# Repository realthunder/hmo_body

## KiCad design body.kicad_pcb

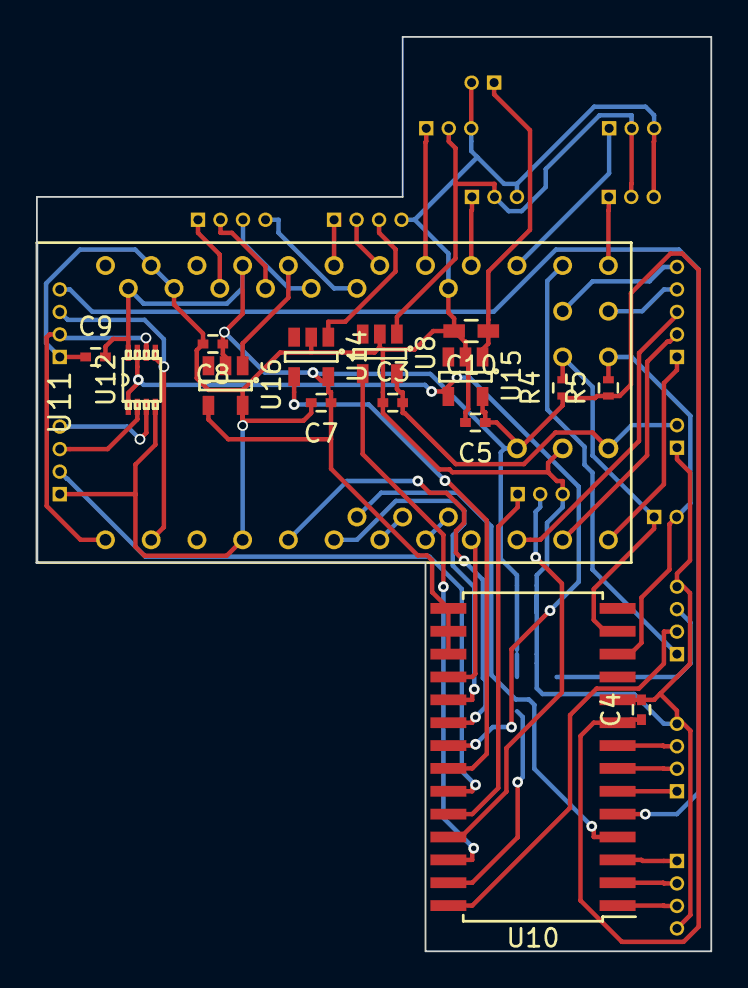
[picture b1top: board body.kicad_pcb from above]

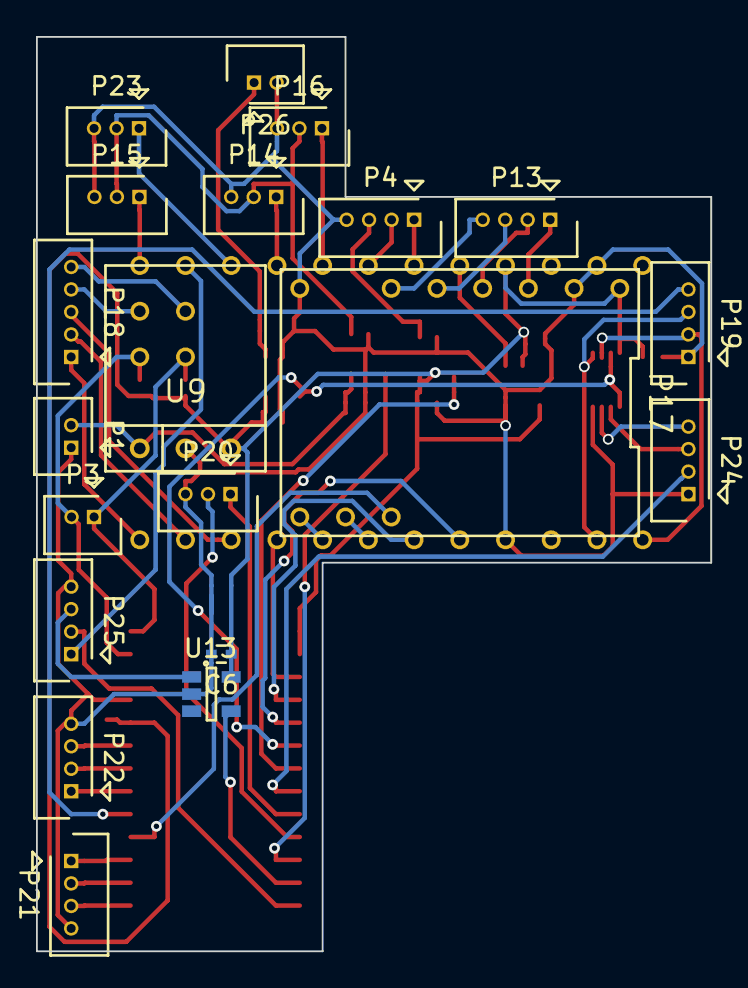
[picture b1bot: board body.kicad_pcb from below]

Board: 2 copper layers, 37.5 x 50.8 mm, 36 parts (20 on the bottom side), 51 nets.

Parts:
C3, C5, C6, C7: 1uF; C_0402
C4, C8, C9: 0.1uF; C_0402
C10: 10uF; C_0603_HandSoldering
P1: CON_VIN; Molex_PicoBlade_53047-0210
P3: CON_I2C; Molex_PicoBlade_53047-0210
P4: CON_LED; Molex_PicoBlade_53047-0410
P13: CON_STEP; Molex_PicoBlade_53047-0410
P14: CON_SRV_CAM; Molex_PicoBlade_53047-0310
P15: CON_SRV_BRAKE; Molex_PicoBlade_53047-0310
P16: CON_SRV_LOCK; Molex_PicoBlade_53047-0310
P17: CON_POLOLU_DRV8834; POLOLU_DRV8834
P18: CON_BAT; Molex_PicoBlade_53047-0510
P19: CON_UART; Molex_PicoBlade_53047-0410
P20: CON_STEP_STOP; Molex_PicoBlade_53047-0310
P21: CON_BTN2; Molex_PicoBlade_53047-0410
P22: CON_BTN1; Molex_PicoBlade_53047-0410
P23: CON_SRV_FOOT; Molex_PicoBlade_53047-0310
P24: CON_EYEPIECE_COM; Molex_PicoBlade_53047-0410
P25: CON_FAN; Molex_PicoBlade_53047-0410
P26: CON_EP_VOUT; Molex_PicoBlade_53047-0210
R4, R5: 10K; R_0402
U8: SRV_SWITCH; SOT-23-5
U9: CON_POLOLU_PWR; POLOLU_U1V10F5
U10: MCP23017; SOIC-28W_7.5x17.9mm_Pitch1.27mm
U11: ProMini; PRO_MINI
U12: 74LVC2G126; TI_DCU_8
U13: FAN_SWITCH; SOT-23-5
U14: LED_SWITCH; SOT-23-5
U15: EP_SWITCH; SOT-23-5
U16: TMP36; SOT-23-5

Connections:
/BAT1_STAT: P18.2, U11.11
/BAT1_VOUT: P18.4, U11.31
/BAT2_STAT: P18.3, U11.10
/BAT2_VOUT: P18.5, U11.32
/BAT_CTL: P18.1, U11.12
/BTN11: P22.1, U10.6
/BTN12: P22.2, U10.7
/BTN13: P22.3, U10.8
/BTN21: P21.1, U10.3
/BTN22: P21.2, U10.2
/BTN23: P21.3, U10.1
/EP_EN: U10.21, U12.1, U12.7, U15.4
/EP_RXD: P24.4, U12.3
/EP_TXD: P24.3, U12.2
/EP_VOUT: C10.1, P26.1, U15.1
/FAN_EN: U10.27, U13.4
/FAN_PWM: P25.1, U11.14
/FAN_TACHO: P25.2, U10.28
/FAN_VOUT: P25.3, U13.1
/FRAME_STOP: P24.2, U10.23
/HOST_INT: P19.4, U10.5
/INTA: U10.20, U11.5
/INTB: U10.19, U11.6
/LED_CLK: P4.1, U11.19
/LED_DAT: P4.2, U11.18
/LED_EN: U10.22, U14.4
/LED_VOUT: P4.3, U14.1
/RXD: P19.3, U11.2, U12.5
/SCL: P3.2, R5.2, U10.12, U11.40
/SDA: P3.1, R4.2, U10.13, U11.39
/SRV_BRAKE: P15.1, U11.13
/SRV_CAM: P14.1, U11.16
/SRV_EN: U8.4, U10.26
/SRV_FOOT: P23.1, U11.15
/SRV_LOCK: P16.1, U11.17
/SRV_VOUT: P14.2, P15.2, P16.2, P23.2, U8.1
/STEP: P17.10, U11.7
/STEP_A1: P13.3, P17.5
/STEP_A2: P13.4, P17.6
/STEP_B1: P13.2, P17.4
/STEP_B2: P13.1, P17.3
/STEP_DIR: P17.9, U11.8
/STEP_STOP1: P20.1, U10.24
/STEP_STOP2: P20.2, U10.25
/TMP: U11.20, U16.1
/TXD: P19.2, U11.1, U12.6
/VIN: C3.2, P1.2, U8.5, U9.1
/~IO_RST: U10.18, U11.9
/~STEP_SLP: P17.11, U10.4
GND: C3.1, C4.2, C5.2, C6.2, C7.2, C8.2, C9.1, C10.2, P1.1, P4.4, P14.3, P15.3, P16.3, P17.2, P17.8, P19.1, P20.3, P21.4, P22.4, P23.3, P24.1, P25.4, P26.2, U8.2, U9.2, U10.10, U11.4, U11.23, U12.4, U13.2, U14.2, U15.2, U16.5
VCC: C4.1, C5.1, C6.1, C7.1, C8.1, C9.2, P17.1, R4.1, R5.1, U9.3, U10.9, U10.15, U10.16, U10.17, U11.21, U12.8, U13.5, U14.5, U15.5, U16.2, U16.4

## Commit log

2016-09-07 Updated design
